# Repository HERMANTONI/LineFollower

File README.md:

# LineFollower
spek singkat :
sensor 8 buah pullup, driver 1 buah, motor 2 buah
pin sensor  A0-A7, Motor kiri D4-D5, Motor kanan D6-D7

tujuan utama:
mampu merekam arena/jalur yang sudah dilalui untuk dibaca kembali ketika menemui jalan buntu

yang ingin berkontribusi silahkan bergabung untuk mengerjakan:
sudah dikerjakan :
1. baca sensor ke biner 👌
2. biner ke pra keputusan 👌
3. pra keputusan ke pid 👌

yang belum :
1. pid ke keputusan dan Motor
2. menentukan pertigaan/perempatan/tikungan
3. menyimpan track yang dilalui
4. membaca kembali track yang dilalui
5. berhenti difinish, kemudian kembali ke posisi start melalui jalur tercepat
6. pembuatan desain mekanik robot mungil tapi kompak.
7. pembuatan desain sensor
8. pembuatan desain sistim minimum
9. pembuatan desain driver mosfet
rencana fitur tambahan:
1. lcd
2. push button
3. gyro
4. kompas
5. bluetooth

jika semisalnya progres sudah sampai 85% dan belum ada kontribusi dan kolab dengan saya,
maka dengan berat hati repo ini akan di buat private kembali 🤷‍♀️.

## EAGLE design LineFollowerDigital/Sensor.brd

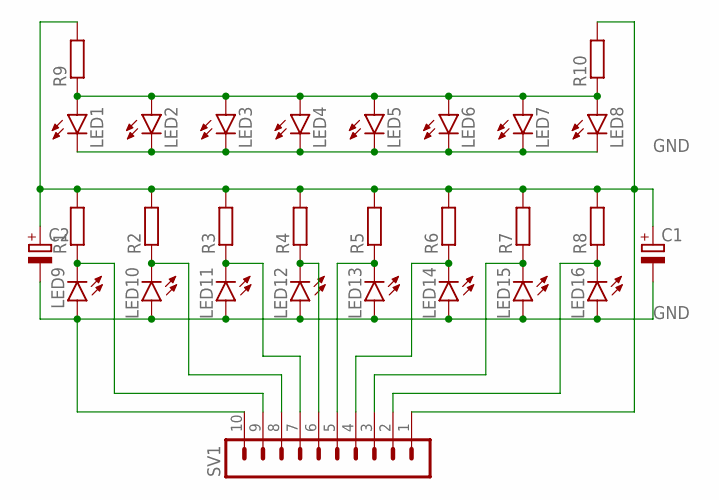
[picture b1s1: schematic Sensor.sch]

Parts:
C1, C2: CPOL-EUE2-4; E2-4
LED1, LED2, LED3, LED4, LED5, LED6, LED7, LED8, LED9, LED10, LED11, LED12, LED13, LED14, LED15, LED16: LED5MM
R1, R2, R3, R4, R5, R6, R7, R8, R9, R10: R-EU_0309/10; 0309/10
SV1: MA10-1

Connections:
GND: C1.-, C2.-, LED1.K (C), LED2.K (C), LED3.K (C), LED4.K (C), LED5.K (C), LED6.K (C), LED7.K (C), LED8.K (C), LED9.A, LED10.A, LED11.A, LED12.A, LED13.A, LED14.A, LED15.A, LED16.A, SV1.10
unnamed: LED9.K (C), R1.1, SV1.9
unnamed: LED10.K (C), R2.1, SV1.8
unnamed: LED11.K (C), R3.1, SV1.7
unnamed: LED12.K (C), R4.1, SV1.6
unnamed: LED13.K (C), R5.1, SV1.5
unnamed: LED14.K (C), R6.1, SV1.4
unnamed: LED15.K (C), R7.1, SV1.3
unnamed: LED16.K (C), R8.1, SV1.2
unnamed: LED1.A, LED2.A, LED3.A, LED4.A, LED5.A, LED6.A, LED7.A, LED8.A, R9.1, R10.1
unnamed: C1.+, C2.+, R1.2, R2.2, R3.2, R4.2, R5.2, R6.2, R7.2, R8.2, R9.2, R10.2, SV1.1

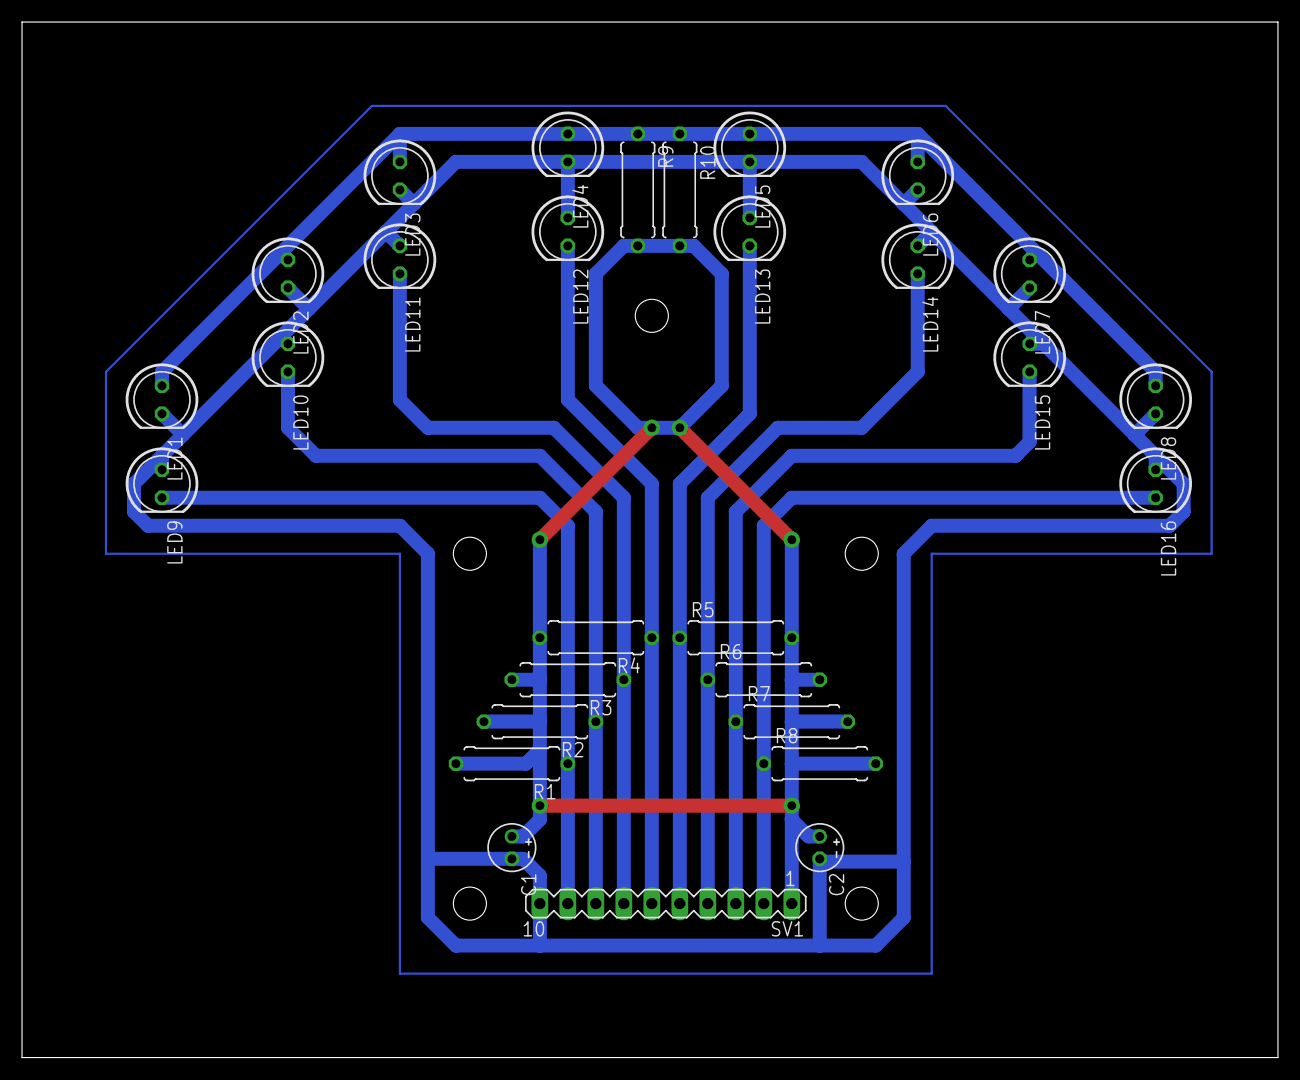
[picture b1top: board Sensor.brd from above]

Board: 2 copper layers, 114.0 x 94.0 mm, 29 parts (0 on the bottom side), 11 nets.

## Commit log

2022-11-05 Create Sensor2Biner
2022-11-05 Rename Sensor2Biner to Sensor2Biner.h
2022-11-05 new file: .vscode/arduino.json new file: .vscode/c_cpp_properties.json new file: Biner2Predecision.h modified: LineFollower.ino modified: Sensor2Biner.h
2022-11-05 submit
2022-11-05 git push
2022-11-08 08 November 2022
2022-11-10 modified: LineFollower.ino new file: LineFollowerDigital/Sensor.b#1 new file: LineFollowerDigital/Sensor.b#2 new file: LineFollowerDigital/Sensor.b#3 new file: LineFollowerDigital/Sensor.b#4 new file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
2022-11-15 modified: .vscode/arduino.json modified: .vscode/c_cpp_properties.json deleted: Biner2Predecision.h new file: Library/Biner2Predecision.h new file: Library/Motor.h new file: Library/PID2Decision.h ne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
2022-11-15 modified: Library/PID2Decision.h modified: Library/Predecision2PID.h modified: Library/Sensor2Biner.h
2022-11-15 16 November 2022
2022-11-22 masih dalam proses
2022-11-22 sementara oke :)
